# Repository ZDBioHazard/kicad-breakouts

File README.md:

Simple Component Breakouts - For KiCAD
--------------------------------------

This is a library of simple breakout boards I've designed for various things.
There are probably pre-existing breakouts out there, but I made my own anyway.

Individual breakout descriptions are in the various project folders. Enjoy.

I tend to get a little carried away with making boards very tiny, so I'm sorry
if they are a bit difficult to assemble. Think of it as soldering practise. :)

The KiCAD files should be mostly self-contained, requiring only the KiCAD
built-in library. I took care to make sure the paths are relative to the
individual projects.

I'm still fairly new at EE, so if you see any electrical problems
with these designs, please let me know so I can learn more. :)

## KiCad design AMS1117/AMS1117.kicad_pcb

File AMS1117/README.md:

AMS1117 Breakout
----------------

This is a small breakout for the
[Advanced Monolithic `AMS1117`](http://www.advanced-monolithic.com/pdf/ds1117.pdf)
series (and compatible) SOT-223 fixed output linear voltage regulators and
their filter capacitors.

The `P1` pinout should be compatible with the usual `78xx` regulators.

Assembly Tips
-------------

The negative ends of `C1` and `C2` are very close together, but they are
connected at the pads anyway, so don't be afraid of bridging them. I designed
this board for reflow assembly, but I managed to get my iron in there anyway.

The `AMS1117` datasheet specifies a tantalum capacitor for `C2`.
Mind the polarity mark.

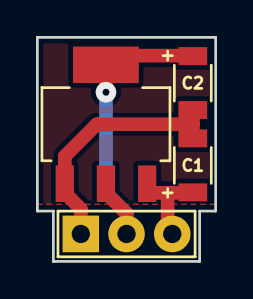
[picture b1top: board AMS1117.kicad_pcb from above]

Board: 2 copper layers, 9.9 x 12.4 mm, 4 parts (0 on the bottom side), 3 nets.

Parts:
C1, C2: 22uF; C_1206
P1: CONN_01X03; Pin_Header_Simple_1x03
U1: AMS1117-3.3; SOT-223

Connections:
GND: C1.2, C2.2, P1.1, U1.1
VCC: C2.1, P1.2, U1.2, U1.4
VDD: C1.1, P1.3, U1.3

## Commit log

2016-06-15 AMS1117: New breakout - First manufacturing.
2016-06-15 XC6206: New breakout - First manufacturing.
2016-06-15 SOT-23: New breakout - First manufacturing.
2016-06-28 AMS1117: Pass the redundant Vout through the via.
2016-07-13 Add README.md files for everything.
2016-07-17 Add a .gitignore file.
2016-08-05 Updated page layout.
